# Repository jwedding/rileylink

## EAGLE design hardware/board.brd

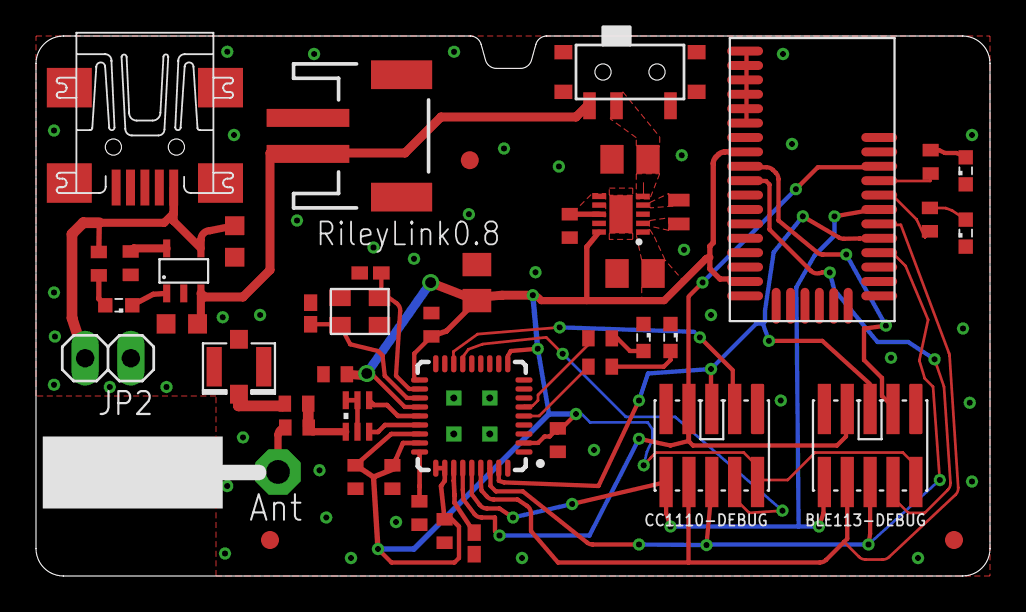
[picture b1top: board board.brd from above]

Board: 2 copper layers, 53.0 x 30.0 mm, 47 parts (0 on the bottom side), 37 nets.

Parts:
ANT1: PAD-01
BLE113-DEBUG: CC-DEBUG-PWR; CC-P05
C1, C7, C8, C10, C12, C13, C14: 0.1uF; C0402
C2, C3: 4.7uF; C0603K
C4, C15: 10 uF; C0805K
C5, C6: 12pF ±5%; C0402K
C9: 1uF; C0402K
C11: 10uF; C0805K
CC1110: CC1110; QLP-36_UPDATE
CC1110-DEBUG: CC-DEBUG-PWR; CC-P05
FID1, FID2, FID3: FIDUCIAL; FIDUCIAL_1MM
IC1: 0915BM15A0001
J1: U.FL
JP1: M02-JST-2MM-SMT; JST-2-SMD
JP2: 1X02
L1: 1.5 uH; INDC1610X12N
LED1: red; SML0603
LED2, LED5: blue; SML0603
LED3, LED4: green; SML0603
PWR: SW_SLIDE; SLIDE_SWITCH_SMD
R1: 2K; R0402
R2: 330; R0402
R3: 56kOhm ± 1%; R0402
R4, R9: R0402
R7, R11, R12, R13: 470 ohms; R0402
REGULATOR: TPS63031; SON50P260X260X80-11N
U1: 5PIN_SOT23
U3: BLE113-A
X1: 24MHz 8pF 10ppm -20C +70C; CTS_32X25
X3: MINI-USB-UX60-MB-5ST; UX60-MB-5ST

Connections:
DC: CC1110.16, CC1110-DEBUG.3
DC_BLE: BLE113-DEBUG.3, U3.P2_2
DD: CC1110.15, CC1110-DEBUG.4
DD_BLE: BLE113-DEBUG.4, U3.P2_1
GND: BLE113-DEBUG.1, C1.2, C2.2, C3.2, C4.2, C5.2, C6.2, C7.2, C8.2, C9.1, C10.2, C11.2, C12.2, C13.2, C14.1, C15.1, CC1110.37, CC1110.38, CC1110.39, CC1110.40, CC1110-DEBUG.1, IC1.2, IC1.5, IC1.6, J1.P$1, J1.P$2, JP1.1, JP2.1, LED2.C, LED3.C, LED4.C, LED5.C, R1.1, R3.1, REGULATOR.3, REGULATOR.9, REGULATOR.11, U1.P$2, U3.GND, U3.GND@2, U3.GND@3, U3.GND@4, U3.GND@5, U3.GND@6, U3.GND@7, U3.GND@8, U3.GND@9, U3.GND@10, X1.2, X1.4, X3.5
MISO: BLE113-DEBUG.10, CC1110.32, CC1110-DEBUG.10, U3.P0_2
MOSI: BLE113-DEBUG.8, CC1110.33, CC1110-DEBUG.8, U3.P0_3
unnamed: L1.1, REGULATOR.2
unnamed: LED1.C, U1.P$1
unnamed: R1.2, U1.P$5
unnamed: LED1.A, R2.2
unnamed: CC1110.24, IC1.3
unnamed: L1.2, REGULATOR.4
unnamed: CC1110.23, IC1.4
unnamed: J1.P$3, R4.1
unnamed: IC1.1, R4.2, R9.1
unnamed: ANT1.1, R9.2
unnamed: C14.2, REGULATOR.6, REGULATOR.7, REGULATOR.8
unnamed: CC1110.27, R3.2
unnamed: C9.2, CC1110.30
unnamed: C6.1, CC1110.21, X1.1
unnamed: C5.1, CC1110.20, X1.3
unnamed: LED4.A, R7.1
unnamed: LED5.A, R11.1
unnamed: LED2.A, R12.1
unnamed: LED3.A, R13.1
unnamed: R12.2, U3.P0_1
unnamed: R13.2, U3.P0_0
P0_0: CC1110.5, R7.2
P0_1: CC1110.6, R11.2
RESET: BLE113-DEBUG.7, CC1110.31, CC1110-DEBUG.7, U3.RESET
SCK: BLE113-DEBUG.6, CC1110.34, CC1110-DEBUG.6, U3.P0_5
SSN: BLE113-DEBUG.5, CC1110.35, CC1110-DEBUG.5, U3.P0_4
V+: C15.2, PWR.COM, REGULATOR.5
VBAT: C3.1, JP1.2, PWR.NC, U1.P$3
VDD: BLE113-DEBUG.2, C1.1, C4.1, C7.1, C8.1, C10.1, C11.1, C12.1, C13.1, CC1110.2, CC1110.10, CC1110.19, CC1110.22, CC1110.25, CC1110.26, CC1110.28, CC1110.29, CC1110-DEBUG.2, REGULATOR.1, REGULATOR.10, U3.AVDD, U3.DVDD
VIN_USB: C2.1, JP2.2, R2.1, U1.P$4, X3.1

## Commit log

2015-08-22 sign change weirdness
2015-08-22 discard results of first read, like the code on master
2015-08-22 Use blue led
2015-08-22 small change to avoid sign change
2015-08-22 specify size during assignment from buffers
2016-04-22 Experiment: fix antenna test point
2016-11-21 Fix bad trace under supply cap

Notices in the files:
parts and their libraries:
parts: Package design from "pretty-eagle-libs" at https://github.com/esden/pretty-eagle-libs/blob/master/pel_misc.lbr by @esden at Github. (CC-BY-SA-3.0)
SparkFun-Connectors: Licensing: Creative Commons ShareAlike 4.0 International - https://creativecommons.org/licenses/by-sa/4.0
